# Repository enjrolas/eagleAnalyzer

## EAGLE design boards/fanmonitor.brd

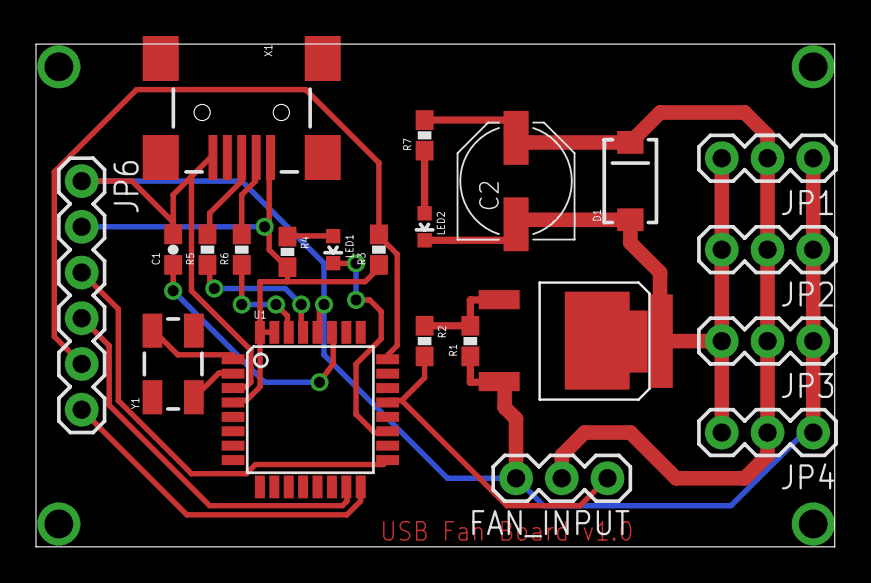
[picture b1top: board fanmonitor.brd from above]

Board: 2 copper layers, 44.4 x 27.9 mm, 22 parts (0 on the bottom side), 20 nets.

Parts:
C1: 1uF; 0603-CAP
C2: 470uF; PANASONIC_D
D1: SMA-DIODE
FAN_INPUT: 1X03
JP1, JP2, JP3, JP4: 1X03
JP6: AVR_MINI_PROG; 1X06
LED1, LED2: LED-0603
R1: 100k; 0603-RES
R2: 1k; 0603-RES
R3: 10K; 0603-RES
R4: 220; 0603-RES
R5, R6: 68; 0603-RES
R7: 680; 0603-RES
U1: ATMEGA8U2AU; TQFP32-08
U$4: RFD14N05L; TO-252AA
X1: USBSMD; USB-MINIB
Y1: CRYSTAL-SMD-5X3

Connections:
5V: JP6.2, R3.1, R4.2, U1.4, U1.31, U1.32, X1.VBUS
/RST: JP6.5, R3.2, U1.24
D+: R5.1, U1.29
D-: R6.1, U1.30
GND: C1.2, FAN_INPUT.3, JP1.1, JP2.1, JP3.1, JP4.1, JP6.1, R1.1, U1.3, U1.28, U$4.3, X1.GND
MISO: JP6.3, U1.17
MOSI: JP6.6, U1.16
unnamed: LED1.A, R4.1
unnamed: LED2.A, R7.1
unnamed: C1.1, U1.27
unnamed: U1.1, Y1.3
unnamed: U1.2, Y1.1
unnamed: R5.2, X1.D+
unnamed: R6.2, X1.D-
PWM: FAN_INPUT.1, R2.2, U1.21
PWM_OUT: C2.-, D1.A, JP1.3, JP2.3, JP3.3, JP4.3, LED2.C, U$4.4
SCK: JP6.4, U1.15
SPD: R1.2, R2.1, U$4.1
STAT: LED1.C, U1.19
VCC: C2.+, D1.C, FAN_INPUT.2, JP1.2, JP2.2, JP3.2, JP4.2, R7.2

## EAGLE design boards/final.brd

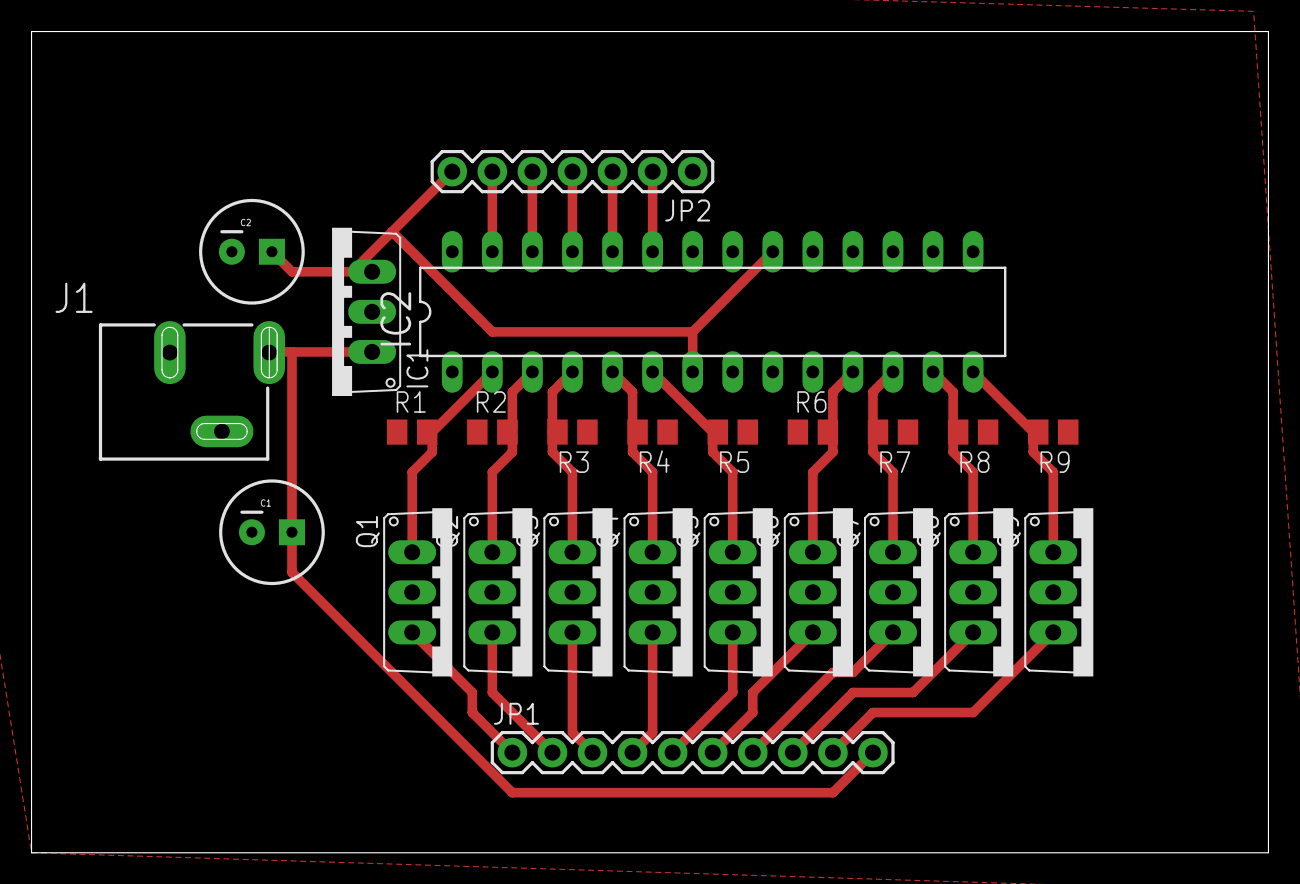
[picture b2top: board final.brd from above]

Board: 2 copper layers, 78.4 x 52.1 mm, 25 parts (0 on the bottom side), 26 nets.

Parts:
C1, C2: CPOL-RADIAL-100UF-25V
IC1: 7805TV; TO220V
IC2: MEGA8-P; DIL28-3
J1: POWER_JACKSLT; POWER_JACK_SLOT
JP1: M10"; 1X10
JP2: 1X07
Q1, Q2, Q3, Q4, Q5, Q6, Q7, Q8, Q9: TO220V
R1, R2, R3, R4, R5, R6, R7, R8, R9: M0805

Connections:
+5V: C2.1, IC1.3, IC2.7, IC2.20, JP2.7
+12V: C1.1, IC1.1, J1.PWR, JP1.10
D0: IC2.2, Q1.1, R1.2
D1: IC2.3, Q2.1, R2.2
D2: IC2.4, Q3.1, R3.2
D3: IC2.5, Q4.1, R4.2
D4: IC2.6, Q5.1, R5.2
D5: IC2.11, Q6.1, R6.2
D6: IC2.12, Q7.1, R7.2
D7: IC2.13, Q8.1, R8.2
D8: IC2.14, Q9.1, R9.2
GND: C1.2, C2.2, IC1.2, IC2.8, IC2.22, J1.GND@2, JP2.1, Q1.2, Q2.2, Q3.2, Q4.2, Q5.2, Q6.2, Q7.2, Q8.2, Q9.2, R1.1, R2.1, R3.1, R4.1, R5.1, R6.1, R7.1, R8.1, R9.1
unnamed: JP1.1, Q1.3
unnamed: JP1.2, Q2.3
unnamed: JP1.3, Q3.3
unnamed: IC2.27, JP2.6
unnamed: IC2.23, JP2.2
unnamed: IC2.24, JP2.3
unnamed: IC2.25, JP2.4
unnamed: IC2.26, JP2.5
unnamed: JP1.4, Q4.3
unnamed: JP1.5, Q5.3
unnamed: JP1.6, Q6.3
unnamed: JP1.7, Q7.3
unnamed: JP1.8, Q8.3
unnamed: JP1.9, Q9.3

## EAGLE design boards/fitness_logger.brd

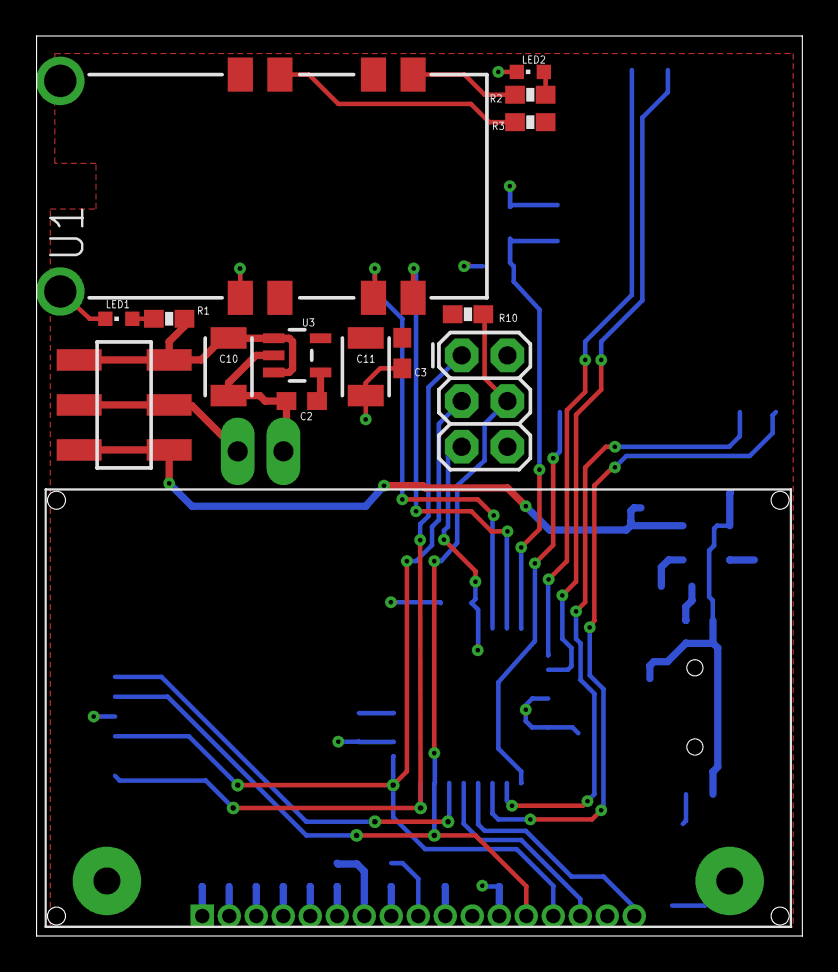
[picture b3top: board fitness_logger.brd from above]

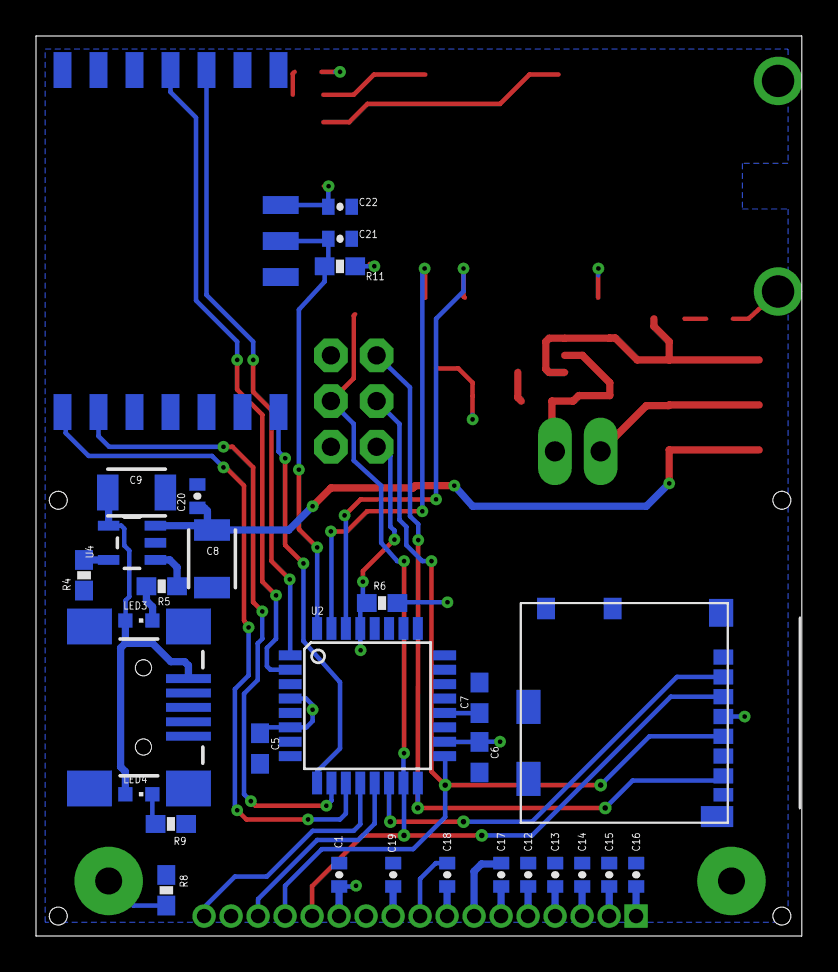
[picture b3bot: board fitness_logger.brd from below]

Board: 2 copper layers, 42.5 x 50.0 mm, 46 parts (30 on the bottom side), 42 nets.

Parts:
C1, C12, C13, C14, C15, C16, C17, C18, C19, C20, C21, C22: 0.1uF; 0402-CAP
C2: C0603
C3, C5, C6, C7: 100nf; C0603
C8, C9, C10, C11: 1210
JP2: 1X02_LONGPADS
LED1, LED2, LED3, LED4: CHIPLED_0603
PRG: AVR_SPI_PRG_6PTH; 2X3
R1, R2, R3, R5, R8, R9, R11: 1k; 0603-RES
R4: 2K; 0603-RES
R6, R10: 10k; 0603-RES
U1: LS20126
U2: ATMEGA168; TQFP32-08
U3: V_REG_LDOSMD; SOT23-5
U4: MCP73831; SOT23-5
U$1: USB-MINIB-5PIN; USB-MINIB
U$2: ANTAP281M4IB
U$3: NHD-C12832A1Z
U$4: MICRO_SD; MICRO_SD_MOLEX
U$5: SPDT; SPDT-SMD

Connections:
A0: U2.13, U$3.P$15
ANT_RST: C21.1, R11.2, U2.32, U$2.2
ANT_RTS: U2.9, U$2.17
ANT_RXD: U2.10, U$2.12
ANT_SLEEP: U2.2, U$2.7
ANT_SUSPEND: U2.1, U$2.6
ANT_TXD: U2.11, U$2.11
CS_DISP: U2.12, U$3.P$17
GND: C1.1, C2.2, C3.2, C5.2, C6.2, C7.2, C8.2, C9.2, C10.2, C11.2, C12.2, C13.2, C14.2, C15.2, C16.2, C19.1, C20.2, C21.2, C22.2, JP2.1, LED1.C, LED2.C, PRG.6, R4.1, R8.1, R9.2, U1.1, U1.9, U1.10, U2.3, U2.5, U2.21, U3.2, U4.2, U$1.GND, U$2.1, U$2.4, U$2.9, U$2.10, U$2.13, U$2.14, U$2.15, U$2.16, U$3.P$11, U$4.6
MISO: PRG.1, U2.16, U$4.7
MOSI: PRG.4, R10.1, U2.15, U$3.P$13, U$4.3
unnamed: C10.1, R1.2, U3.1, U3.3, U$5.1, U$5.4
unnamed: C2.1, U3.4
unnamed: LED1.A, R1.1
unnamed: C9.1, LED3.A, LED4.A, U4.4, U$1.VBUS
unnamed: LED2.A, R2.1
unnamed: R2.2, U1.5
unnamed: JP2.2, U$5.2, U$5.5
unnamed: C8.1, C20.1, U4.3, U$5.3, U$5.6
unnamed: R3.1, U1.7
unnamed: R4.2, U4.5
unnamed: C7.1, U2.20
unnamed: LED3.C, R5.2
unnamed: R5.1, U4.1
unnamed: C12.1, U$3.P$5
unnamed: C13.1, U$3.P$4
unnamed: C14.1, U$3.P$3
unnamed: C15.1, U$3.P$2
unnamed: C16.1, U$3.P$1
unnamed: C17.1, U$3.P$6
unnamed: C17.2, U$3.P$7
unnamed: C19.2, U$3.P$10
unnamed: C18.1, U$3.P$8
unnamed: R8.2, U$3.P$18
unnamed: C18.2, U$3.P$9
unnamed: LED4.C, R9.1
RESET: PRG.5, R6.1, U2.29
RXD: U1.3, U2.30
SCK: PRG.3, U2.17, U$3.P$14, U$4.5
SS: U2.14, U$4.2
TXD: U1.4, U2.31
VCC: C1.2, C3.1, C5.1, C6.1, C11.1, C22.1, R3.2, R6.2, R10.2, R11.1, U1.2, U1.8, U2.4, U2.6, U2.18, U3.5, U$2.3, U$3.P$12, U$3.P$16, U$3.P$19, U$4.4

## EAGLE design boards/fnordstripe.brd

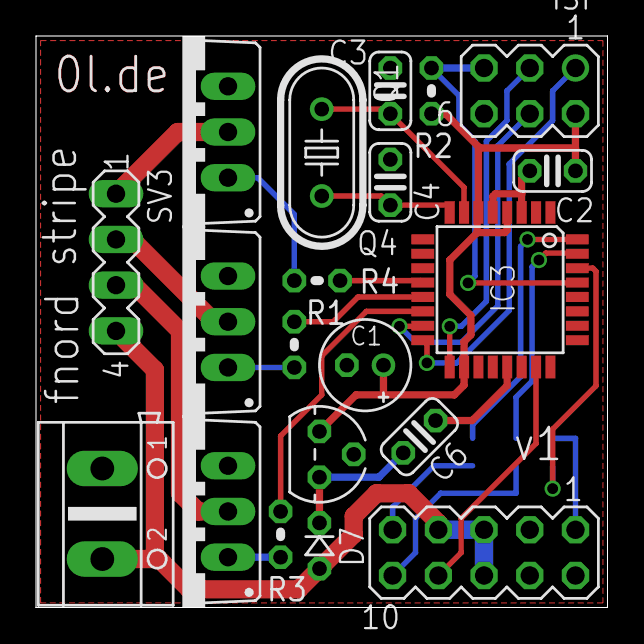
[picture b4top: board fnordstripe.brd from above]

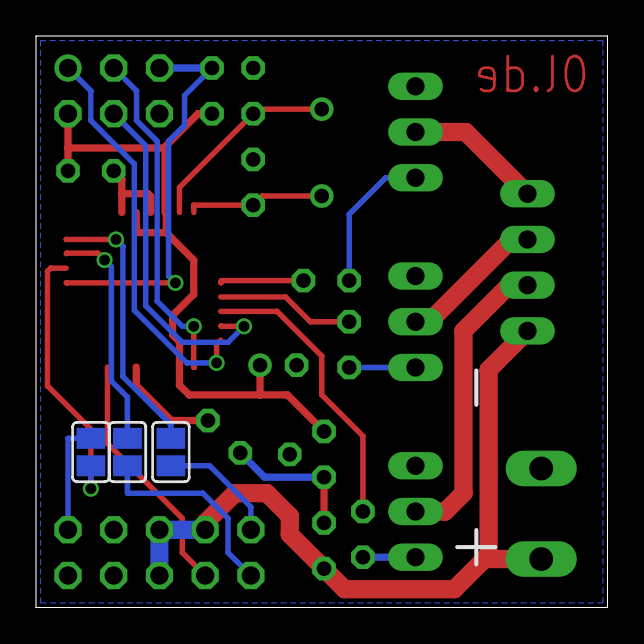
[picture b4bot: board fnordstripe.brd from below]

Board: 2 copper layers, 31.8 x 31.8 mm, 23 parts (3 on the bottom side), 26 nets.

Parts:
BUS: MA05-2
C1: 47uF; E2-5
C2, C6: 100n; C025-024X044
C3, C4: 33p; C025-024X044
D7: D-2.5
IC2: 78L05Z; TO92
IC3: MEGA8-AI; TQFP32-08
ISP: MA03-2
Q1: 16MHz; HC49U-V
Q2, Q3, Q4: IRF540; TO220BV
R1, R3, R4: 50; 0204V
R2: 2k2; 0204V
SJ1, SJ2, SJ3: SJ
SV3: MA04-1
X1: AK500/2

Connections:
+5V: C1.+, C2.1, IC2.1, IC3.4, IC3.6, IC3.18, ISP.2, R2.1
+12V: BUS.5, BUS.6, BUS.7, D7.A, SV3.4, X1.2
ADC0: BUS.8, IC3.23
BLUE: IC3.14, R3.2
BUSINT: BUS.9, SJ3.2
DATA1: BUS.10, SJ2.2
DATA2: BUS.1, SJ1.2
GND: BUS.2, BUS.3, BUS.4, C1.-, C2.2, C3.2, C4.2, C6.2, IC2.2, IC3.3, IC3.5, IC3.21, ISP.6, Q2.S, Q3.S, Q4.S, X1.1
GREEN: IC3.13, R1.2
INT0: IC3.32, SJ3.1
MISO: IC3.16, ISP.1
MOSI: IC3.15, ISP.4
unnamed: Q2.G, R1.1
unnamed: Q3.G, R3.1
unnamed: Q3.D, SV3.3
unnamed: Q4.G, R4.2
unnamed: Q2.D, SV3.2
unnamed: Q4.D, SV3.1
unnamed: C6.1, D7.C, IC2.3
RED: IC3.12, R4.1
RST: IC3.29, ISP.5, R2.2
RX: IC3.30, SJ1.1
SCK: IC3.17, ISP.3
TX: IC3.31, SJ2.1
XTAL1: C3.1, IC3.7, Q1.1
XTAL2: C4.1, IC3.8, Q1.2

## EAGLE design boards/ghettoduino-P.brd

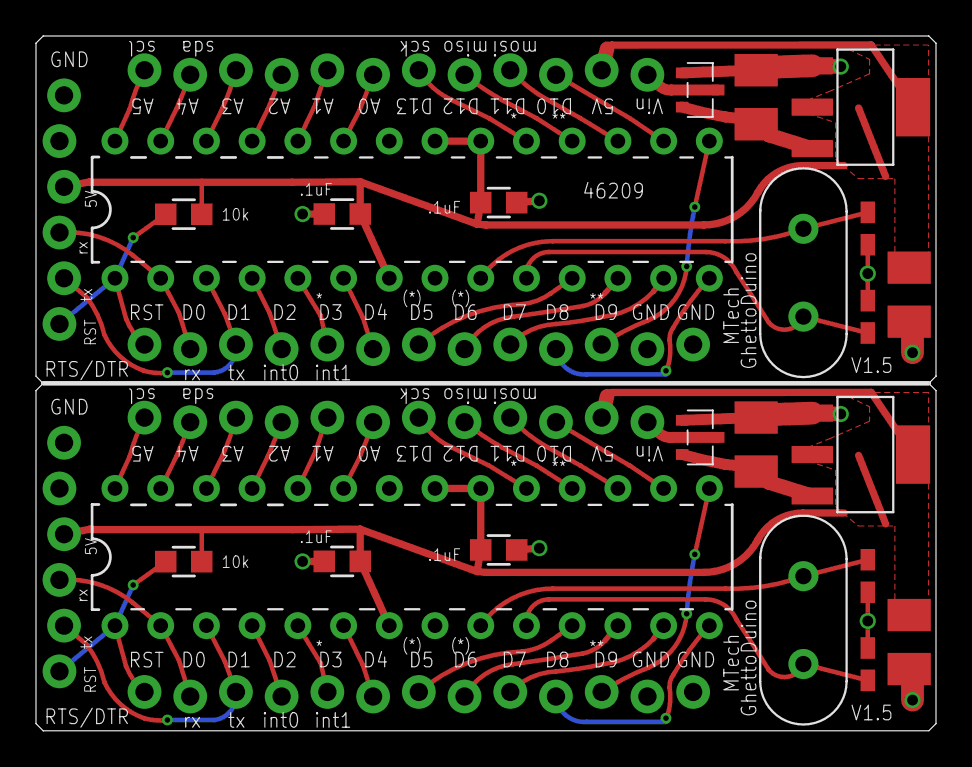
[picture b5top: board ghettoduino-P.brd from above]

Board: 2 copper layers, 50.0 x 38.6 mm, 28 parts (0 on the bottom side), 54 nets.

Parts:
5V, 5V1: 5V-LDO-ZLDO1117; ZLDO1117
C1, C3, C6, C7: 18pF; 0603-CAP
C2, C4, C9, C10: .1uF; 0805
C5, C8, C11, C12: 10uF; 1206
IC1, IC2: DIL28-3
JP1, JP2: 1X06_LOCK
R1, R2: 10k; 0805
U$1, U$4: HC49US
U$2, U$6: M12; 1X13_LOCK
U$3, U$8: P-MOSFET-PMV48XP; SOT23-3LEAD
U$5, U$7: M12; 1X12_LOCK

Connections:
5V: 5V.2, 5V.4, C2.2, C4.1, C5.1, IC1.7, IC1.20, IC1.21, JP1.4, R1.1, U$5.11
5V1: 5V1.2, 5V1.4, C9.2, C10.1, C11.1, IC2.7, IC2.20, IC2.21, JP2.4, R2.1, U$7.11
A0: IC1.23, U$5.6
A1: IC1.24, U$5.5
A2: IC1.25, U$5.4
A3: IC1.26, U$5.3
A4: IC1.27, U$5.2
A5: IC1.28, U$5.1
A6: IC2.28, U$7.1
A7: IC2.27, U$7.2
A8: IC2.26, U$7.3
A9: IC2.25, U$7.4
A10: IC2.24, U$7.5
A11: IC2.23, U$7.6
D0: IC1.2, JP1.3, U$2.2
D1: IC1.3, JP1.2, U$2.3
D2: IC1.4, U$2.4
D3: IC1.5, U$2.5
D4: IC1.6, U$2.6
D5: IC1.11, U$2.7
D6: IC1.12, U$2.8
D7: IC1.13, U$2.9
D8: IC1.14, U$2.10
D9: IC1.15, U$2.11
D10: IC1.16, U$5.10
D11: IC1.17, U$5.9
D12: IC1.18, U$5.8
D13: IC1.19, U$5.7
D14: IC2.4, U$6.4
D15: IC2.5, U$6.5
D16: IC2.6, U$6.6
D17: IC2.11, U$6.7
D18: IC2.12, U$6.8
D19: IC2.13, U$6.9
D20: IC2.14, U$6.10
D21: IC2.15, U$6.11
D22: IC2.16, U$7.10
D23: IC2.17, U$7.9
D24: IC2.18, U$7.8
D25: IC2.19, U$7.7
D26: IC2.2, JP2.3, U$6.2
D27: IC2.3, JP2.2, U$6.3
GND: 5V.1, C1.1, C2.1, C3.1, C4.2, C5.2, C8.2, IC1.8, IC1.22, JP1.5, JP1.6, U$2.12, U$2.13, U$3.1
GND1: 5V1.1, C6.1, C7.1, C9.1, C10.2, C11.2, C12.2, IC2.8, IC2.22, JP2.5, JP2.6, U$6.12, U$6.13, U$8.1
unnamed: U$3.3, U$5.12
unnamed: U$7.12, U$8.3
RESET: IC1.1, JP1.1, R1.2, U$2.1
RESET1: IC2.1, JP2.1, R2.2, U$6.1
VIN: 5V.3, C8.1, U$3.2
VIN1: 5V1.3, C12.1, U$8.2
XTAL_N: C3.2, IC1.10, U$1.2
XTAL_N1: C6.2, IC2.10, U$4.2
XTAL_P: C1.2, IC1.9, U$1.1
XTAL_P1: C7.2, IC2.9, U$4.1

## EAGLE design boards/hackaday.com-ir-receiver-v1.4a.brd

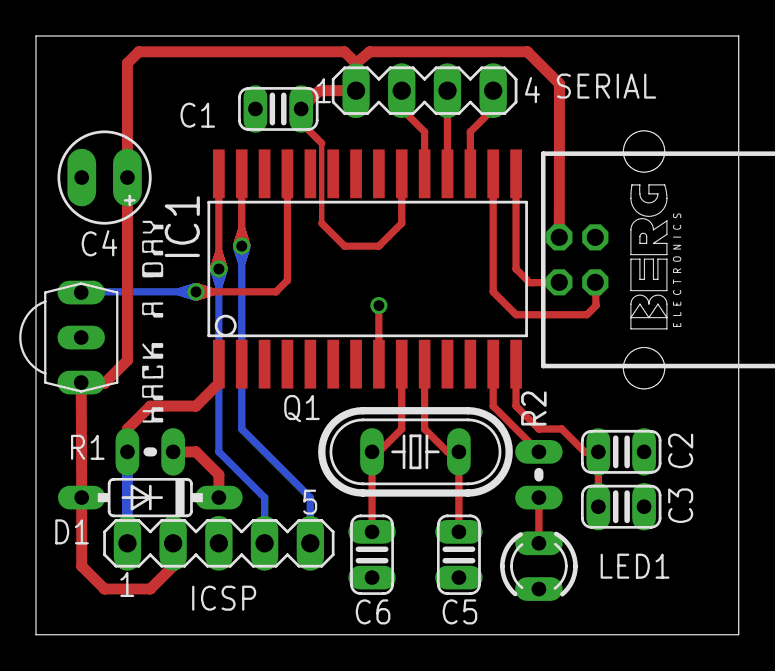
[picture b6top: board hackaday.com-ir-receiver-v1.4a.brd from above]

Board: 2 copper layers, 39.0 x 33.3 mm, 17 parts (0 on the bottom side), 16 nets.

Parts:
C1, C2, C3: 0.1uf; C025-024X044
C4: 4.7Uf; E2,5-5
C5, C6: 27pf; C025-024X044
D1: 1N4148DO35-7; DO35-7
IC1: PIC18F2455_28W; SO28W
ICSP: MA05-1
LED1: LED3MM
Q1: 20Mhz; HC49U-V
R1: 10k; 0204V
R2: 330R; 0204V
SERIAL: MA04-1
TSOP-1738: TSOP4838; TSOP18XX
U$1: HACKADAY-TEXT-ONLY
USB: PN61729

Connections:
CLKI: C6.1, IC1.9, Q1.2
CLKO: C5.1, IC1.10, Q1.1
GND: C1.2, C2.2, C3.2, C4.-, C5.2, C6.2, IC1.8, IC1.19, ICSP.3, LED1.K, SERIAL.2, TSOP-1738.GND, USB.4
IRDATA: IC1.25, TSOP-1738.OUT
MCLR: IC1.1, ICSP.1, R1.1
unnamed: C2.1, C3.1, IC1.14
unnamed: IC1.17, SERIAL.4
unnamed: IC1.18, SERIAL.3
unnamed: LED1.A, R2.1
unnamed: D1.C, R1.2
unnamed: IC1.13, R2.2
PGC: IC1.27, ICSP.5
PGD: IC1.28, ICSP.4
RC4: IC1.15, USB.2
RC5: IC1.16, USB.3
VCC: C1.1, C4.+, D1.A, IC1.20, ICSP.2, SERIAL.1, TSOP-1738.VCC, USB.1

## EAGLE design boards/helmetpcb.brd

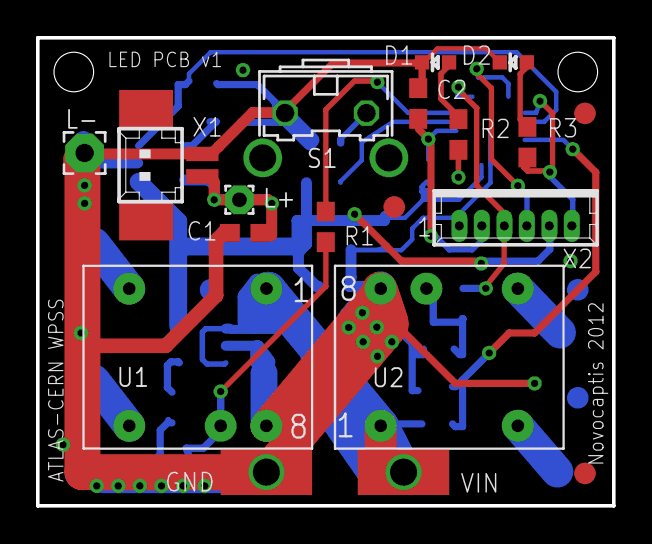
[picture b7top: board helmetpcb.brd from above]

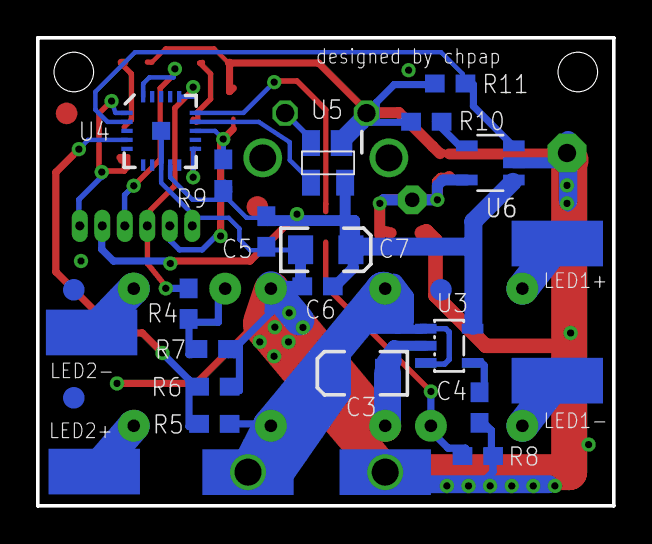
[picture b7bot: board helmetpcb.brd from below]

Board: 2 copper layers, 32.0 x 26.0 mm, 39 parts (23 on the bottom side), 24 nets.

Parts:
C1: 1uF; C0603
C2, C4, C5, C6: 0.1uF; 0603
C3, C7: 10uF; EIA3216
D1: Red; LED-0603
D2: Green; LED-0603
GND: WIREPADSMD2,54-5,08; SMD2,54-5,08
L+: WIREPAD1,6/0,8; 1,6/0,8
L-: WIREPAD2,15/1,0; 2,15/1,0
LED1+, LED1-, LED2+, LED2-: SMD2,54-5,08
R1, R4: 30K; 0603
R2, R3: 330; 0603
R5: 330K; 0603
R6: 220k; 0603
R7, R8, R9: 10K; 0603
R10, R11: 10k; 0603
S1: BTN; B3F-31XX
U1, U2: LDU0516S350
U3: LP2992; SOT23-5
U4: ATTINY84A; QFN20
U5: MAX6816; SOT143
U6: FPF2106; SOT23-5
VIN, VIN1: WIREPADSMD2,54-5,08; SMD2,54-5,08
X1: 53398-02
X2: 53047-06
_GND: WIREPADSMD2,54-5,08; SMD2,54-5,08

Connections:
+5V: C5.2, C6.1, C7.A, R9.2, U3.5, U4.9, U5.4, U6.1, X2.5
BAT: R5.1, R6.2, U4.4
BUTTON: U4.14, U5.3
GND: C1.2, C2.2, C3.C, C4.2, C5.1, C6.2, C7.C, D1.C, D2.C, GND.1, L-.1, R6.1, R7.2, R8.1, R10.1, R11.1, S1.2, U1.8, U2.8, U3.2, U4.0, U4.8, U5.1, U6.2, X1.1, X2.1, _GND.1
LED: R2.2, U4.11
LED+: LED2+.1, U2.4
LED-: LED2-.1, U2.5
LIGHTPWM: R1.2, U4.15
LUXLED1+: LED1+.1, U1.4
LUXLED1-: LED1-.1, U1.5
MISO: U4.20, X2.4
MOSI: R4.2, U4.16, X2.3
N4: R11.2, U4.2, U6.3
unnamed: R1.1, R8.2, U1.7
unnamed: D1.A, R2.1
unnamed: R10.2, U6.4
unnamed: C1.1, L+.1, U6.5, X1.2
unnamed: S1.1, U5.2
unnamed: D2.A, R3.2
unnamed: R4.1, R7.1, U2.7
unnamed: C4.1, U3.4
RAW: C3.A, R5.2, U1.1, U2.1, U3.1, U3.3, VIN.1, VIN1.1
RESET: C2.1, R9.1, U4.13, X2.2
SCK: R3.1, U4.1, X2.6

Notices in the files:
parts and their libraries:
SparkFun-DigitalIC: Licensing: CC v3.0 Share-Alike You are welcome to use this library for commercial purposes.
